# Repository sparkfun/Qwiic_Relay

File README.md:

SparkFun Qwiic Single Relay
========================================

[*SparkFun Qwiic Single Relay (COM-15093)*](https://www.sparkfun.com/products/15093)
Have you ever wanted to control something powerful? Have you ever needed to turn on/off a high voltage device from your Arduino? Now you can with the Qwiic Relay! This device allows you to control large power loads with simple I<sup>2</sup>C commands. The Qwiic Relay can handle 10 Amps at 120 Volts AC, perfect for large inductive loads like DC motors or blenders.

The Qwiic Relay comes with a default I<sup>2</sup>C address but can be changed with a simple command allowing you to control over 100 Qwiic Relays on a single bus!<sup>[1](#powerWarning)</sup>

The Qwiic Relay comes fully assembled and uses the simple [Qwiic](https://www.sparkfun.com/qwiic) interface. No soldering, no voltage translation, no figuring out which pin is SDA or SCL, just plug and go!

<div class="alert alert-warning"><b>Note:</b> Controlling high voltage (110/220VAC) requires certain precautions. A beginner can do it but if you're unsure then please consider the pre-made <a href="https://www.sparkfun.com/products/14236">IoT Power Relay</a>. It's not I<sup>2</sup>C but the IoT Power Relay contains shielding to prevent accidental shock.</div>

Footnote 1: Toggling lots of relays on a 3.3V bus can cause voltage spikes. An external power supply will be required.

Repository Contents
-------------------

* **/Documents** - Datasheets
* **/Firmware** - Latest firmware and examples. 
* **/Hardware** - Eagle design files (.brd, .sch)

Documentation
--------------
* **[Hookup Guide](https://learn.sparkfun.com/tutorials/qwiic-single-relay-hookup-guide)** - Basic hookup guide

Arduino Library
--------------
* **[SparkFun Qwiic Relay Arduino Library](https://github.com/sparkfun/SparkFun_Qwiic_Relay_Arduino_Library)** - SparkFun Arduino Library for controlloing the Qwiic Single and Quad Relay

License Information
-------------------

This product is _**open source**_! 

Please review the LICENSE.md file for license information. 

If you have any questions or concerns on licensing, please contact techsupport@sparkfun.com.

Please use, reuse, and modify these files as you see fit. Please maintain attribution to SparkFun Electronics and release under the same license.

Distributed as-is; no warranty is given.

- Your friends at SparkFun.

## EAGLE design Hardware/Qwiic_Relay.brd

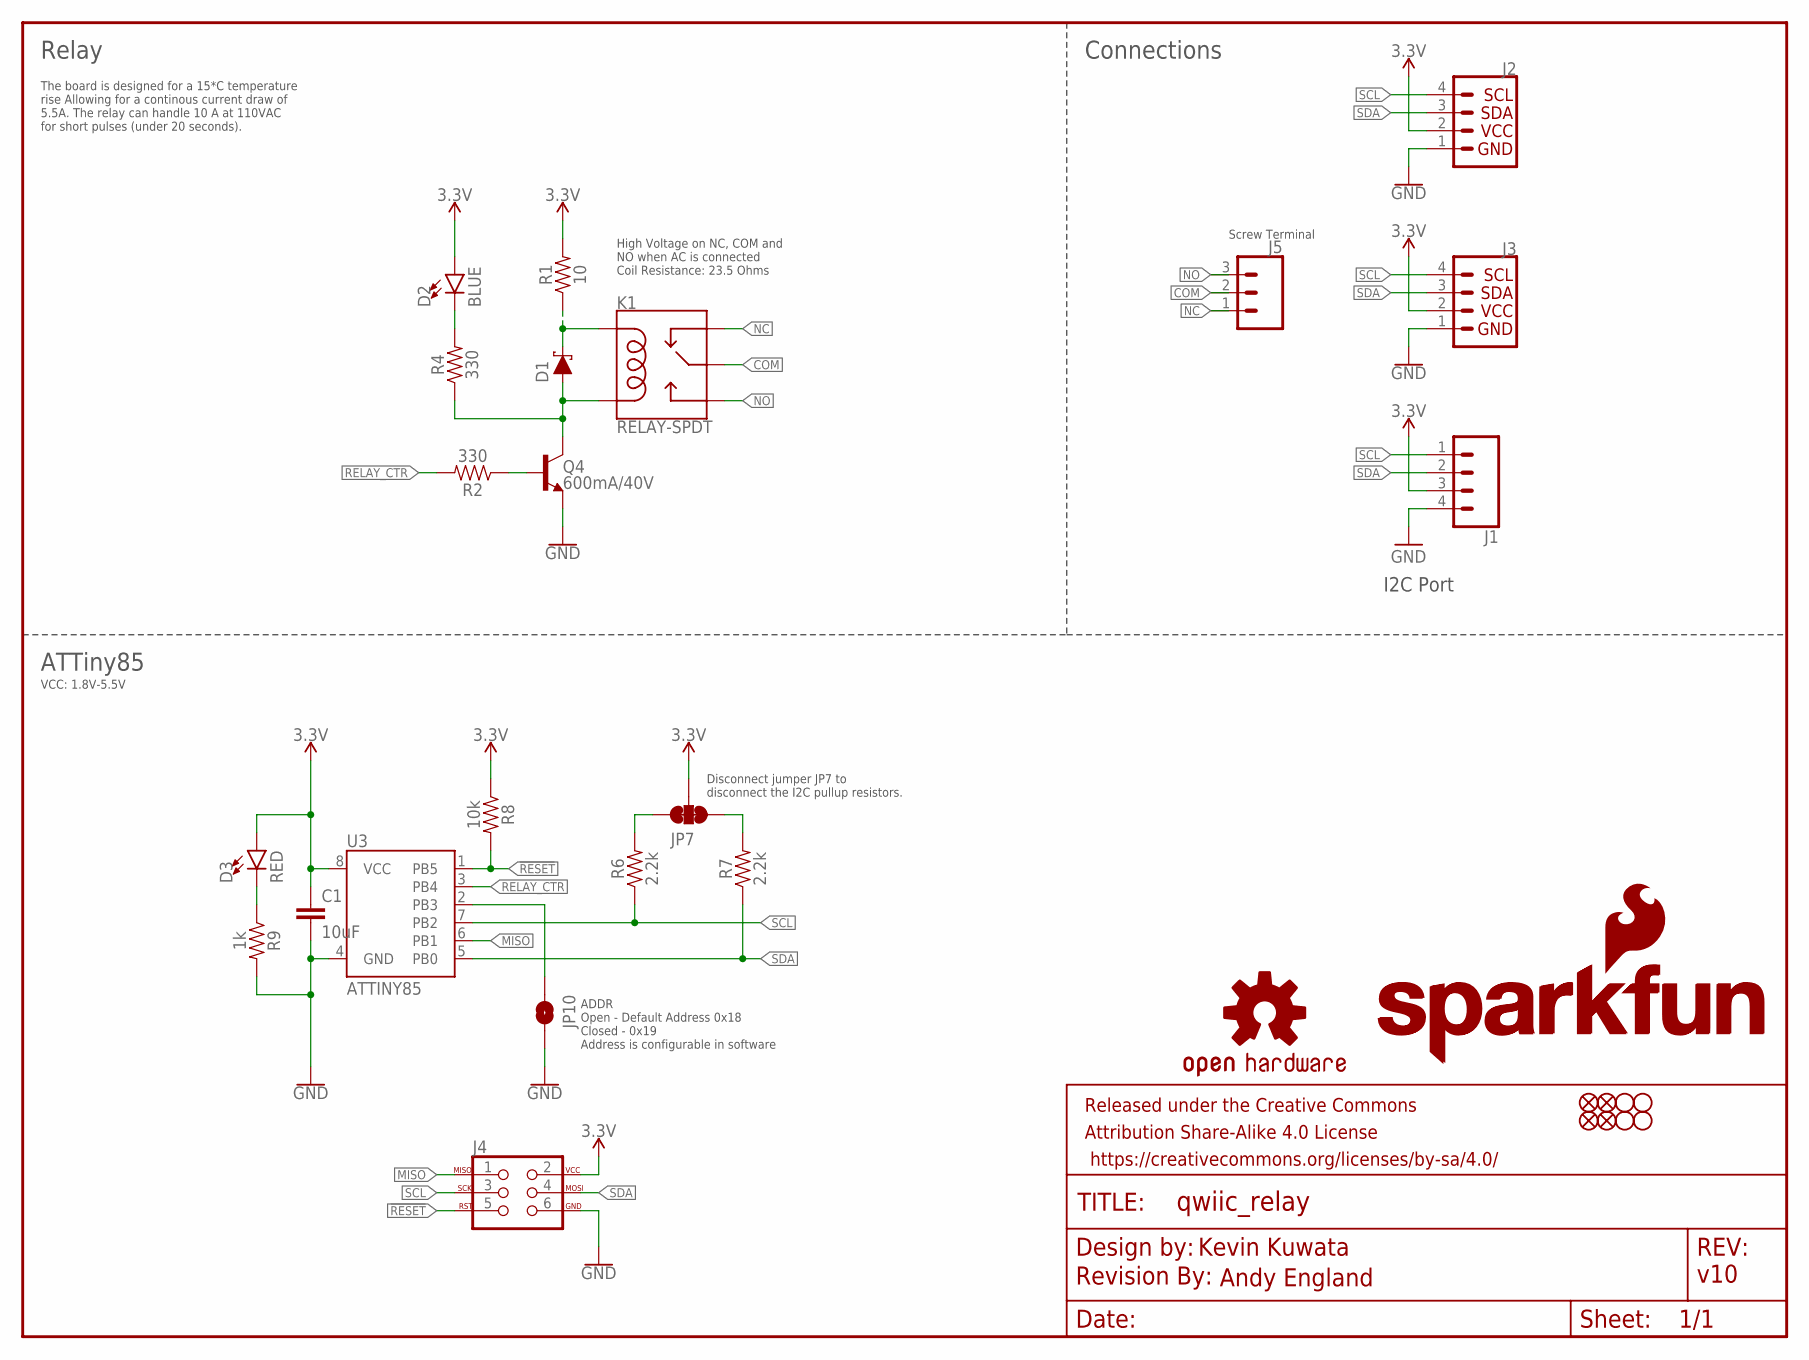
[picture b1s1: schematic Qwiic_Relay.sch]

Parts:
C1: 10uF; 0603
D1: 1A/23V/620mV; SOD-323
D2: BLUE; LED-0603
D3: RED; LED-0603
FRAME1: FRAME-LETTER; CREATIVE_COMMONS
J1: CONN_041X04_NO_SILK; 1X04_NO_SILK
J2, J3: QWIIC_CONNECTORJS-1MM; 1X04_1MM_RA
J4: AVR_SPI_PROG_3X2TESTPOINTS; 2X3_TEST_POINTS
J5: CONN_03-SCREW-5MM; SCREWTERMINAL-5MM-3
JP1, JP3, JP4, JP5: STAND-OFF
JP2, JP6, JP8, JP9: FIDUCIALUFIDUCIAL; MICRO-FIDUCIAL
JP7: JUMPER-SMT_3_2-NC_TRACE_NO-SILK; SMT-JUMPER_3_2-NC_TRACE_NO-SILK
JP10: JUMPER-SMT_2_NO_NO-SILK; SMT-JUMPER_2_NO_NO-SILK
K1: RELAY-SPDT; RELAY_G5LE
LOGO1: OSHW-LOGOMINI; OSHW-LOGO-MINI
LOGO2: REVISION
Q4: 600mA/40V; SOT23-3
R1: 10; 0603
R2, R4: 330; 0603
R6, R7: 2.2k; 0603
R8: 10k; 0603
R9: 1k; 0603
U3: ATTINY85
U$3: SFE_LOGO_NAME.1_INCH; SFE_LOGO_NAME_.1
U$4: SFE_LOGO_NAME_FLAME.1_INCH; SFE_LOGO_NAME_FLAME_.1

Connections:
3.3V: C1.1, D2.A, D3.A, J1.3, J2.2, J3.2, J4.2, JP7.2, R1.2, R8.1, U3.8 (VCC)
!RESET: J4.5, R8.2, U3.1 (PB5)
COM: J5.2, K1.1 (MAIN)
GND: C1.2, J1.4, J2.1, J3.1, J4.6, JP10.2, Q4.2 (E), R9.2, U3.4 (GND)
MISO: J4.1, U3.6 (PB1)
unnamed: Q4.1 (B), R2.1
unnamed: D1.A, K1.5 (COIL2), Q4.3 (C), R4.1
unnamed: JP7.1, R7.2
unnamed: JP10.1, U3.2 (PB3)
unnamed: D1.C, K1.2 (COIL1), R1.1
unnamed: D2.C, R4.2
unnamed: JP7.3, R6.2
unnamed: D3.C, R9.1
NC: J5.1, K1.4 (NC)
NO: J5.3, K1.3 (NO)
RELAY_CTR: R2.2, U3.3 (PB4)
SCL: J1.1, J2.4, J3.4, J4.3, R6.1, U3.7 (PB2)
SDA: J1.2, J2.3, J3.3, J4.4, R7.1, U3.5 (PB0)

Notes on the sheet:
Kevin Kuwata
v10
Screw Terminal
I2C Port
The board is designed for a 15*C temperature rise Allowing for a continous current draw of 5.5A. The relay can handle 10 A at 110VAC for short pulses (under 20 seconds).
ADDR Open - Default Address 0x18 Closed - 0x19 Address is configurable in software
Andy England
ATTiny85
Relay
Connections
Disconnect jumper JP7 to disconnect the I2C pullup resistors.
VCC: 1.8V-5.5V
High Voltage on NC, COM and NO when AC is connected Coil Resistance: 23.5 Ohms

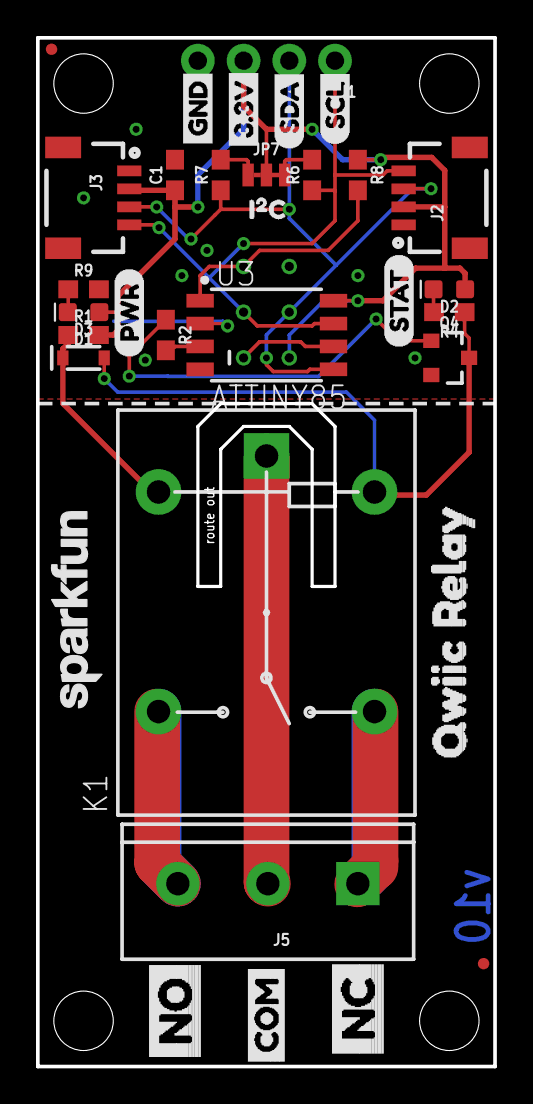
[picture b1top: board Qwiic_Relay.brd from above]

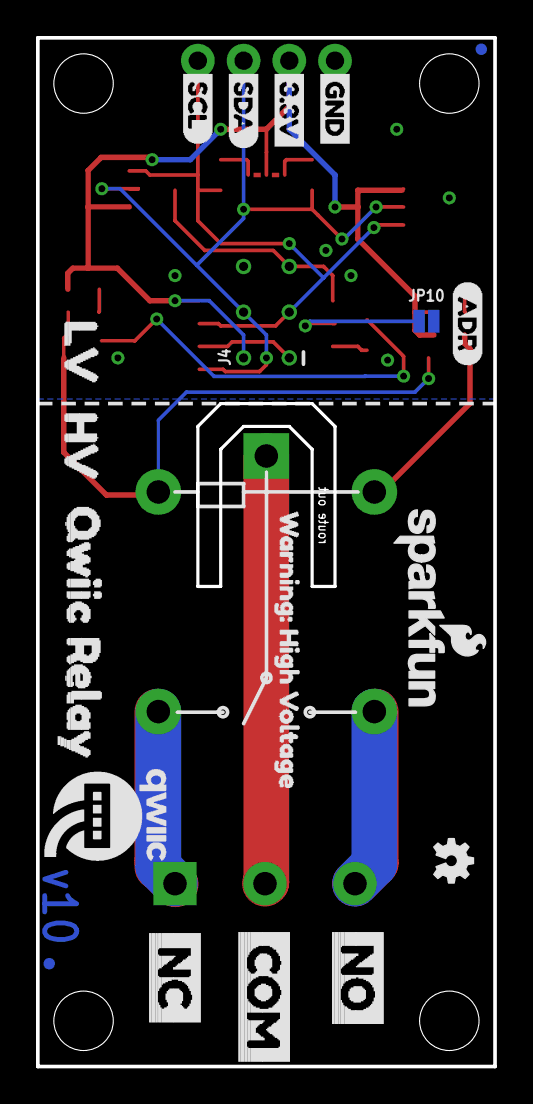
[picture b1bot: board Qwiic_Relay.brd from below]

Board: 2 copper layers, 25.4 x 57.1 mm, 60 parts (19 on the bottom side), 18 nets.

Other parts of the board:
U$1: QWIIC-LOGO-MEDIUM
U$2: (PWR)
U$5: SCL
U$6: SDA
U$7, U$22: 3.3V
U$8, U$13: GND
U$9: (ADR)
U$10: ORDERING_INSTRUCTIONS
U$11, U$18: NO2
U$12: COM7
U$14: I__C1
U$15, U$16: _QWIIC_RELAY0
U$17, U$20: NC3
U$19: COM4
U$21: 20
U$23: SCL1
U$24: SDA0
U$25: STAT1
U$26: WARNING#_HIGH_VOLTAGE0
U$27: HV2
U$28: LV1

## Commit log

2018-11-12 pre review
2018-11-13 changing to most recent rev
2018-11-14 post review
2018-11-15 post-qc review
2018-11-19 moving high voltage silk
2018-12-27 updating prod_id of relay to proper prod_id
2019-01-02 adding example code
2019-07-02 Removes Example Code which now lives in the SparkFun Qwiic Relay Arduino Library, and updates the readme with a link to it

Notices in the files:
parts and their libraries:
SparkFun-Capacitors: Licensing: Creative Commons ShareAlike 4.0 International - https://creativecommons.org/licenses/by-sa/4.0
SparkFun-Aesthetics: Released under the Creative Commons Attribution Share-Alike 4.0 License
SparkFun-Aesthetics: https://creativecommons.org/licenses/by-sa/4.0
